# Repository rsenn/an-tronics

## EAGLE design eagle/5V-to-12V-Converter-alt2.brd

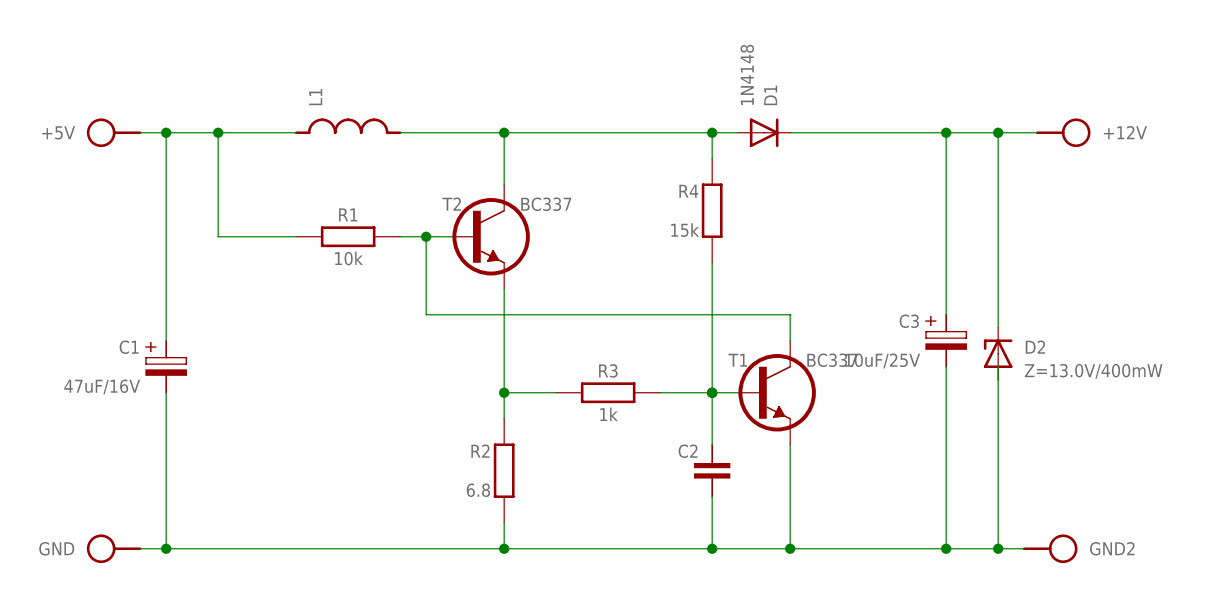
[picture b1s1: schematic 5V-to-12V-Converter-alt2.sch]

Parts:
+5V, +12V: SPAD
C1: 47uF/16V; E2.5-4/V
C2: C050-025X075
C3: 10uF/25V; E2.5-4/V
D1: 1N4148; DO34-7
D2: Z=13.0V/400mW; DO34Z10V
GND, GND2: SPAD
L1: L-SHORT02/5; L-02/5V
R1: 10k; 0204/10
R2: 6.8; 0204/10
R3: 1k; 0204/10
R4: 15k; 0204/10
T1, T2: BC337; TO92-CBE

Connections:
unnamed: R1.2, T1.C, T2.B
unnamed: +5V.1, C1.+, L1.2, R1.1
unnamed: +12V.1, C3.+, D1.C, D2.C
unnamed: C1.-, C2.2, C3.-, D2.A, GND.1, GND2.1, R2.1 (2), T1.E
unnamed: R2.2 (1), R3.1, T2.E
unnamed: C2.1, R3.2, R4.1 (2), T1.B
unnamed: D1.A, L1.1, R4.2 (1), T2.C

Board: 2 copper layers, 16 parts (0 on the bottom side), 7 nets, no tracks yet.

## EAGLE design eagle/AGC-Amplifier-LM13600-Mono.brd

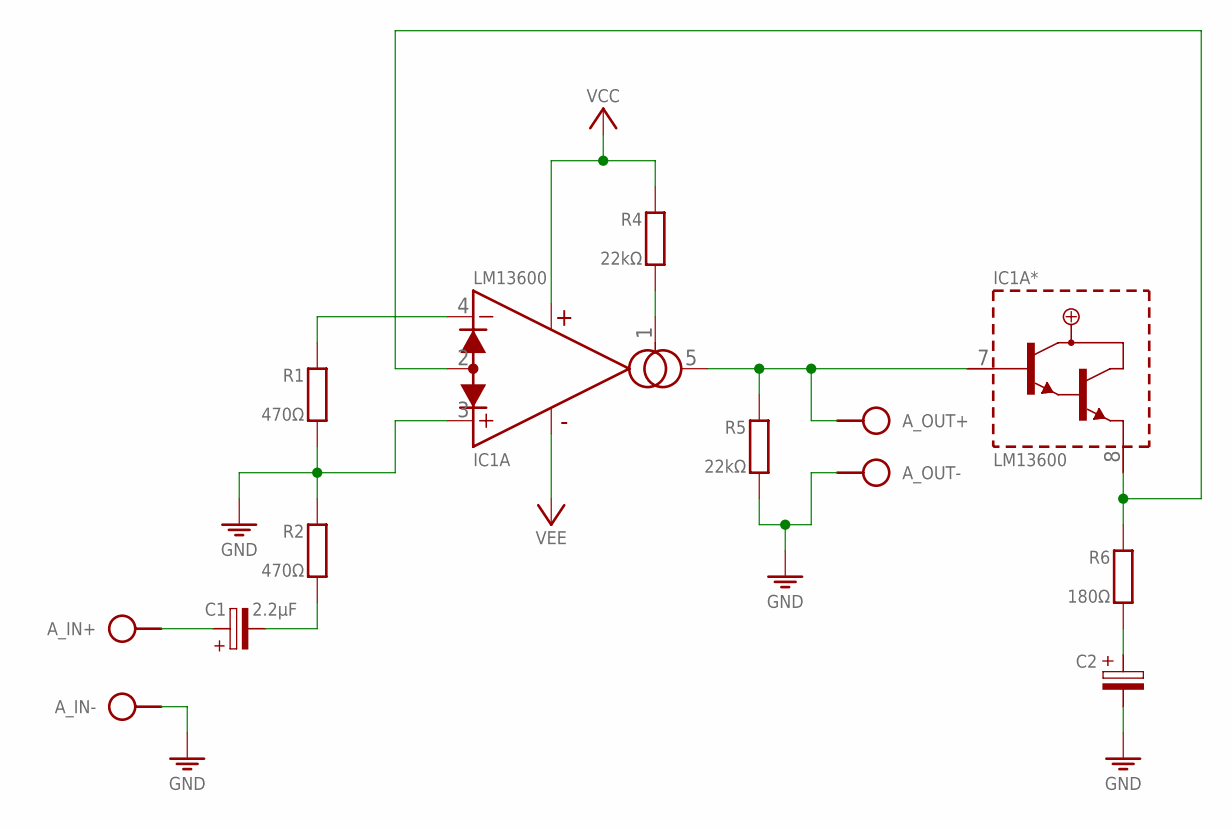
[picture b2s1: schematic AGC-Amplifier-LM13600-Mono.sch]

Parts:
A_IN: SPAD+-+-; SPAD+-
A_OUT: SPAD+-+-; SPAD+-
C1: 2.2μF; E2.5-4/V
C2: CPOLE2,5-4/V; E2.5-4/V
IC1: LM13600; DIL16
PWR: VCC_GND_VEEPWR-+GND-; SPAD-PWR-+GND-
R1: 470Ω; 0202/7
R2: 470Ω; 0202/7-V
R4: 22kΩ; 0202/7
R5: 22kΩ; 0202/7-V
R6: 180Ω; 0202/7

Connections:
GND: A_IN.1, A_OUT.1, C2.-, IC1.3 (+IN), PWR.GND, R1.2, R2.1, R5.2
unnamed: IC1.1 (AMP/BIAS), R4.2
unnamed: C1.-, R2.2
unnamed: C2.+, R6.2
unnamed: IC1.4 (-IN), R1.1
unnamed: IC1.2 (DIODE/BIAS), IC1.8 (BUFF/OUT), R6.1
unnamed: A_IN.2, C1.+
unnamed: A_OUT.2, IC1.5 (OUT), IC1.7 (BUFF/IN), R5.1
VCC: IC1.11 (V+), PWR.VCC, R4.1
VEE: IC1.6 (V-), PWR.VEE

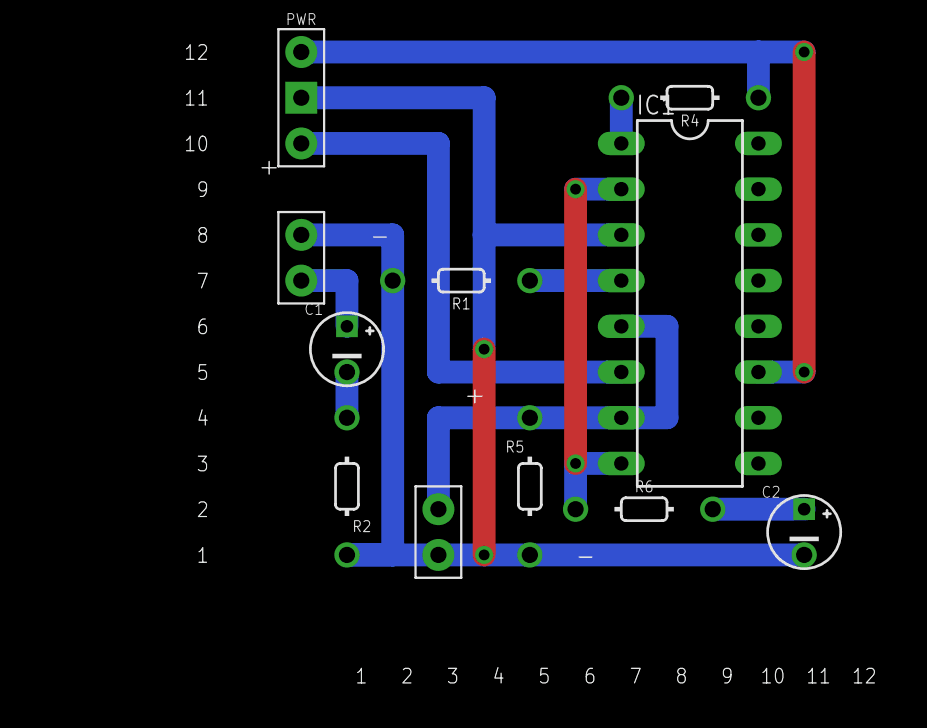
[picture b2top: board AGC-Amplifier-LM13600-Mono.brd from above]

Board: 2 copper layers, 11 parts (0 on the bottom side), 10 nets.

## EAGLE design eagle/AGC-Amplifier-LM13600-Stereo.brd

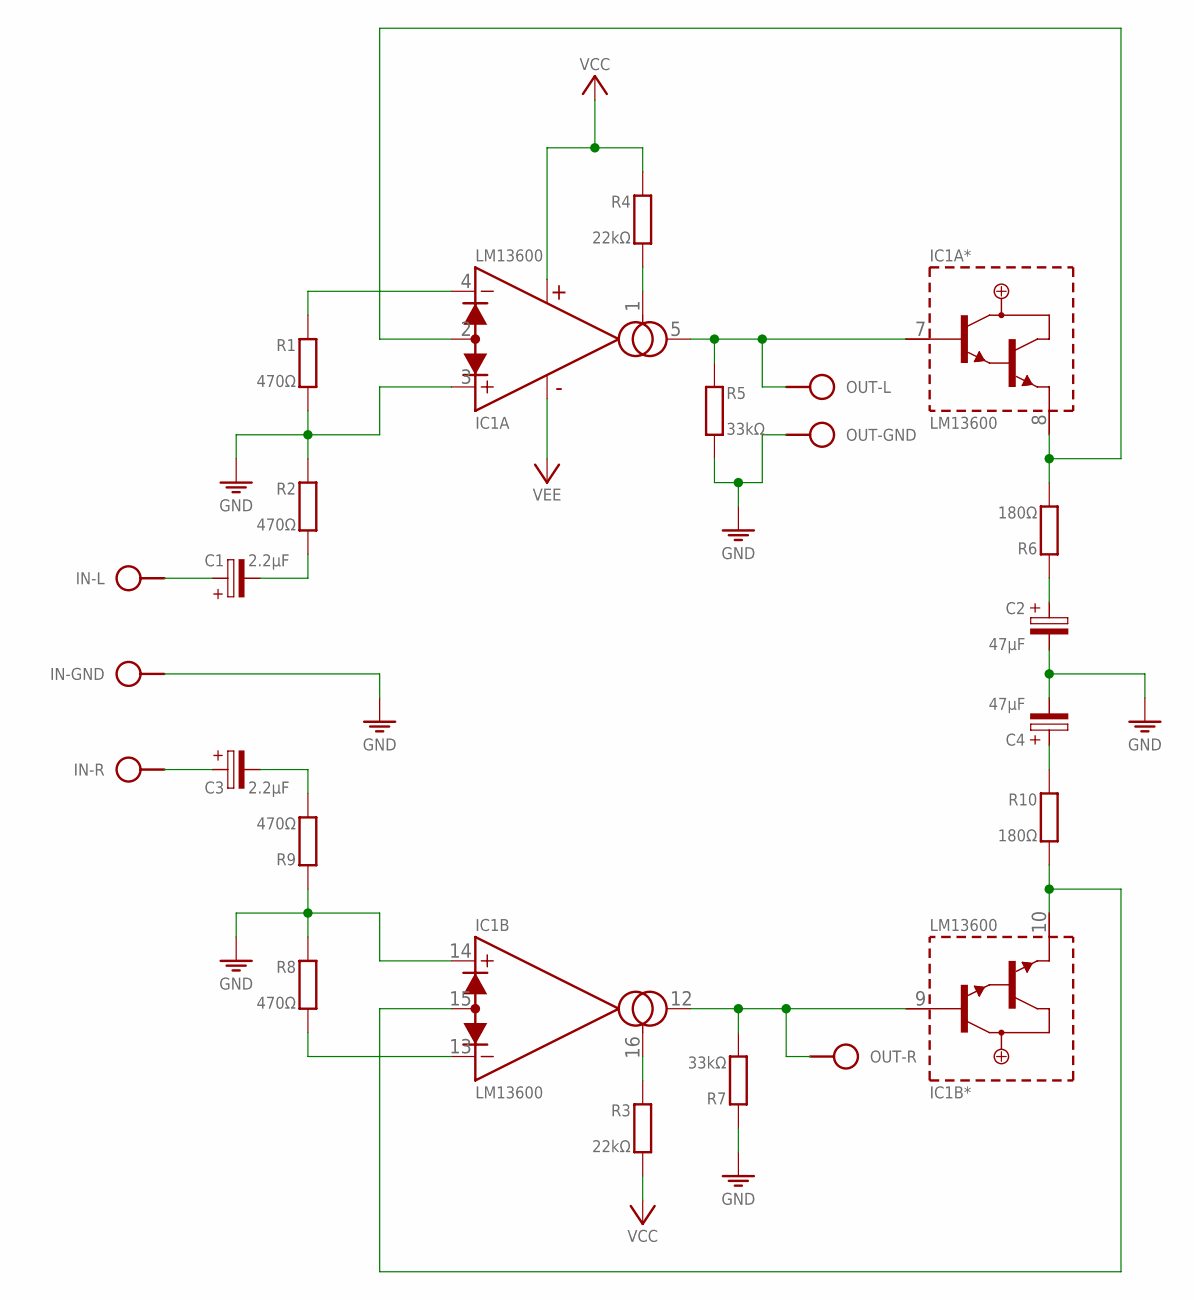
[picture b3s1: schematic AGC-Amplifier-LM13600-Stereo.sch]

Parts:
C1, C3: 2.2μF; E2,5-4
C2, C4: 47μF; E2.5-4/V
IC1: LM13600; DIL16
IN: SAUDIOL-GND-R; SPAD-L-GND-R
OUT: SAUDIO; SPAD-3
PWR: VCC_GND_VEEPWR--GND+; SPAD-PWR--GND+
R1, R8, R9: 470Ω; 0202/7-V
R2: 470Ω; 0202/7
R3, R4: 22kΩ; 0202/7
R5, R7: 33kΩ; 0202/7-V
R6, R10: 180Ω; 0202/7-V

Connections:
GND: C2.-, C4.-, IC1.3 (+IN), IC1.14 (+IN), IN.0, OUT.2, PWR.GND, R1.2, R2.1, R5.2, R7.1, R8.1, R9.1
unnamed: IC1.1 (AMP/BIAS), R4.2
unnamed: C1.-, R2.2
unnamed: C2.+, R6.1
unnamed: IC1.4 (-IN), R1.1
unnamed: IC1.2 (DIODE/BIAS), IC1.8 (BUFF/OUT), R6.2
unnamed: C1.+, IN.L
unnamed: IC1.5 (OUT), IC1.7 (BUFF/IN), OUT.1, R5.1
unnamed: IC1.16 (AMP/BIAS), R3.1
unnamed: C3.-, R9.2
unnamed: IC1.13 (-IN), R8.2
unnamed: IC1.10 (BUFF/OUT), IC1.15 (DIODE/BIAS), R10.2
unnamed: C4.+, R10.1
unnamed: IC1.9 (BUFF/IN), IC1.12 (OUT), OUT.3, R7.2
unnamed: C3.+, IN.R
VCC: IC1.11 (V+), PWR.VCC, R3.2, R4.1
VEE: IC1.6 (V-), PWR.VEE

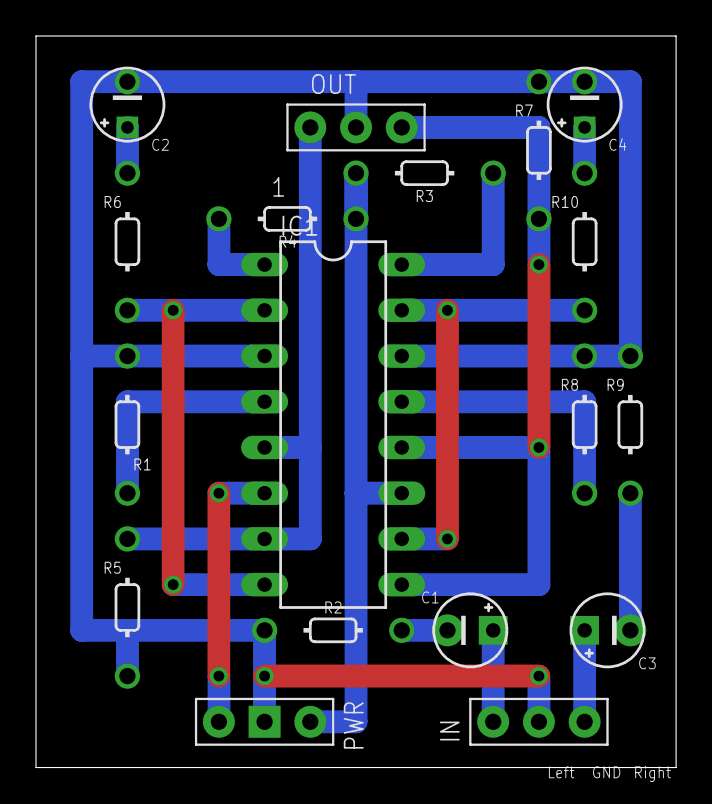
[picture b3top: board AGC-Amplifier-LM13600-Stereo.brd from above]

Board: 2 copper layers, 35.6 x 40.6 mm, 18 parts (0 on the bottom side), 17 nets.

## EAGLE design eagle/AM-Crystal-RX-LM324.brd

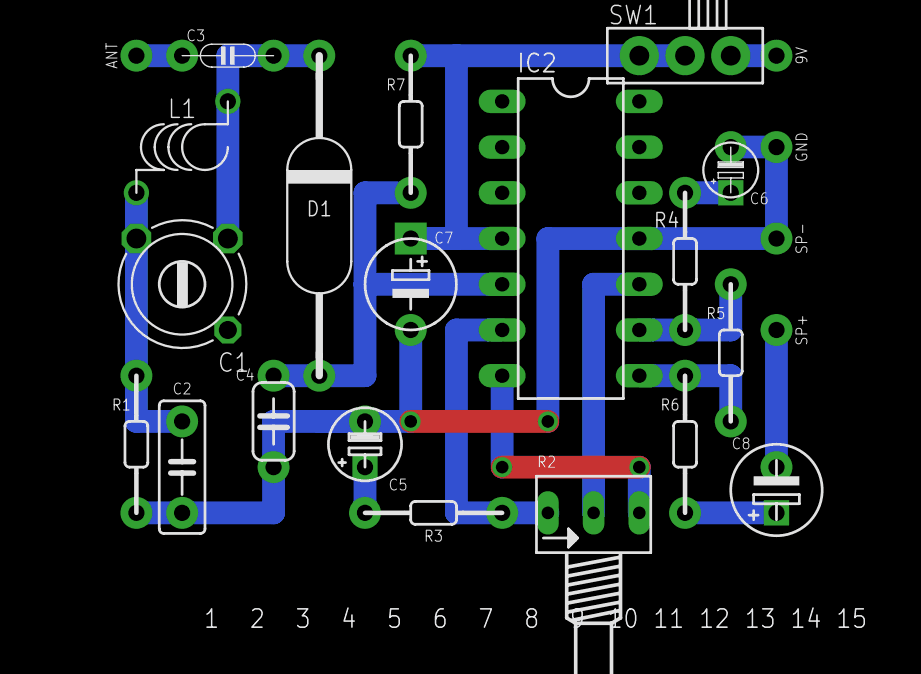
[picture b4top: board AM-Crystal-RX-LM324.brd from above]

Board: 2 copper layers, 24 parts (0 on the bottom side), 16 nets.

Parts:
9V: BAT+; SPAD
ANT: ANT; SPAD
C1: 5-18pF; TRIM808-45
C2: 10nF; C050-025X075/V
C3: 1.5pF; C050-020X036
C4: 330pF; C050-024X044/V
C5: 1μF; E2.5-4/V
C6: 1μF; E2,5-3/V
C7: 100μF; E5-5/V
C8: 100μF; E2,5-5/V
D1: OA79; OA79-18/V
GND: BAT-; SPAD
IC2: LM324; DIL14
L1: 0.15μH; L-04-5/5
R1, R7: 1MΩ; 0202/7-V
R2: 100kΩ; B64Y
R3: 3.3kΩ; 0202/7
R4: 3.3kΩ; 0202/7-V
R5: 100kΩ; 0202/7-V
R6: 100Ω; 0202/7-V
SP+: SPKR+; SPAD
SP-: SPKR-; SPAD
SW1: SL-SW-1P-2T-H; SLSW-1P2T-H

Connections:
A: IC2.7, R2.A
E: IC2.6, R2.E, R3.1
GND: C2.2, C4.2, C5.-, C6.-, C7.-, GND.1, IC2.11, R1.2, SP-.1
unnamed: C4.1, D1.A, IC2.5, R7.2
unnamed: C7.+, IC2.4, R7.1, SW1.P
unnamed: C1.1, C2.1, L1.1, R1.1
unnamed: C1.2, C3.2, D1.C, L1.2
unnamed: ANT.1, C3.1
unnamed: IC2.8, R5.2, R6.1
unnamed: IC2.9, R4.1, R5.1
unnamed: C5.+, R3.2
unnamed: C6.+, R4.2
unnamed: C8.+, R6.2
unnamed: C8.-, SP+.1
unnamed: 9V.1, SW1.O
S: IC2.10, R2.S

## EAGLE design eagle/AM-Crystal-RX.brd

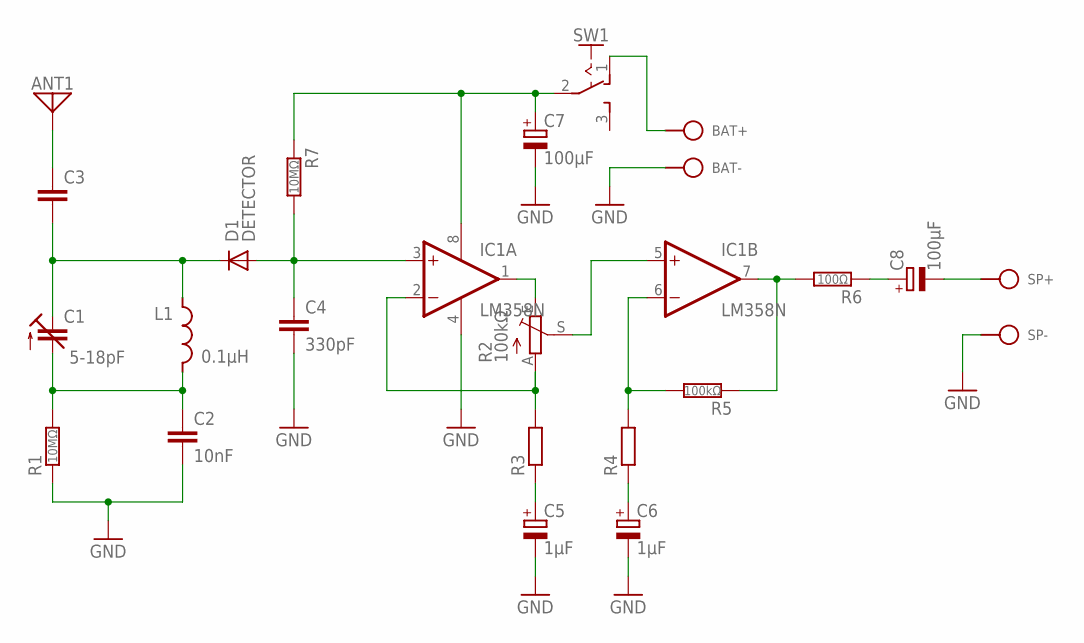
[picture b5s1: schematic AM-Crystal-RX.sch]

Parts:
ANT1: ANT; SPAD
BAT+: BAT+; SPAD
BAT-: BAT-; SPAD
C1: 5-18pF; TRIM-2222-808
C2: 10nF; C050-025X075
C3: C025-015X024
C4: 330pF; C050-024X044
C5, C6: 1μF; E2,5-3
C7, C8: 100μF; E2,5-5
D1: DETECTOR; DO34-10
IC1: LM358N; DIL08
L1: 0.1μH; L-04/10
R1: 10MΩ; 0202/7-V
R2: 100kΩ; B64Y
R3, R4: R0202/7; 0202/7
R5: 100kΩ; 0202/7
R6: 100Ω; 0202/7
R7: 10MΩ; 0202/7
SP+: SPKR+; SPAD
SP-: SPKR-; SPAD
SW1: SL-SW-1P-2T-H; SLSW-1P2T-H

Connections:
GND: BAT-.1, C2.2, C4.2, C5.-, C6.-, C7.-, IC1.4 (V-), R1.1, SP-.1
unnamed: C4.1, D1.A, IC1.3 (+IN), R7.2
unnamed: C7.+, IC1.8 (V+), R7.1, SW1.2
unnamed: C1.2 (E), C2.1, L1.2, R1.2
unnamed: IC1.2 (-IN), R2.A, R3.2
unnamed: C1.1 (A), C3.2, D1.C, L1.1
unnamed: ANT1.1, C3.1
unnamed: IC1.1 (OUT), R2.E
unnamed: IC1.5 (+IN), R2.S
unnamed: IC1.7 (OUT), R5.1, R6.2
unnamed: IC1.6 (-IN), R4.2, R5.2
unnamed: C5.+, R3.1
unnamed: C6.+, R4.1
unnamed: C8.+, R6.1
unnamed: C8.-, SP+.1
unnamed: BAT+.1, SW1.1 (O)

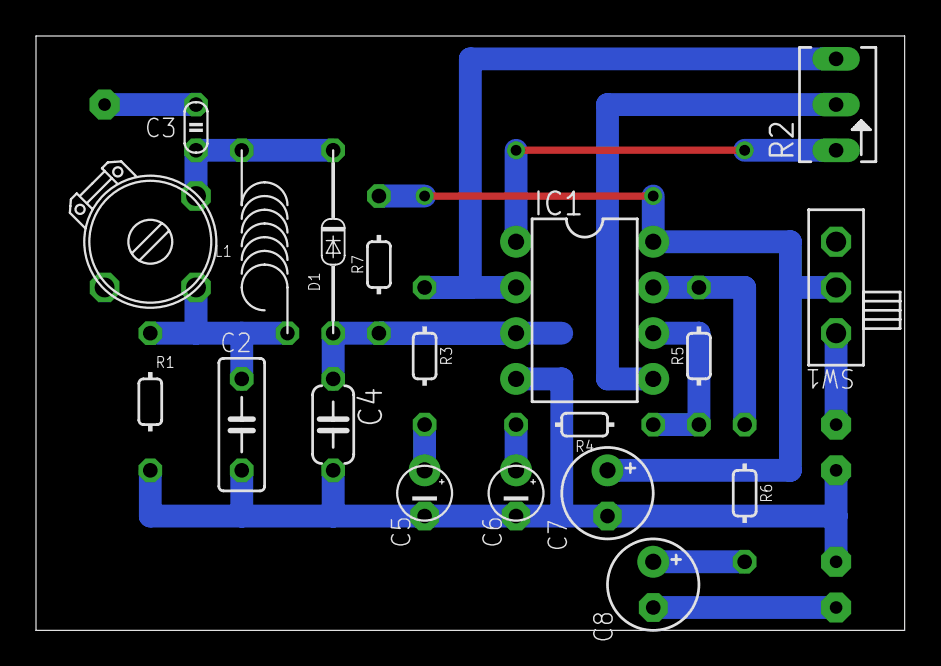
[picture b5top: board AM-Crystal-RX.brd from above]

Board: 2 copper layers, 48.3 x 33.0 mm, 24 parts (0 on the bottom side), 16 nets.

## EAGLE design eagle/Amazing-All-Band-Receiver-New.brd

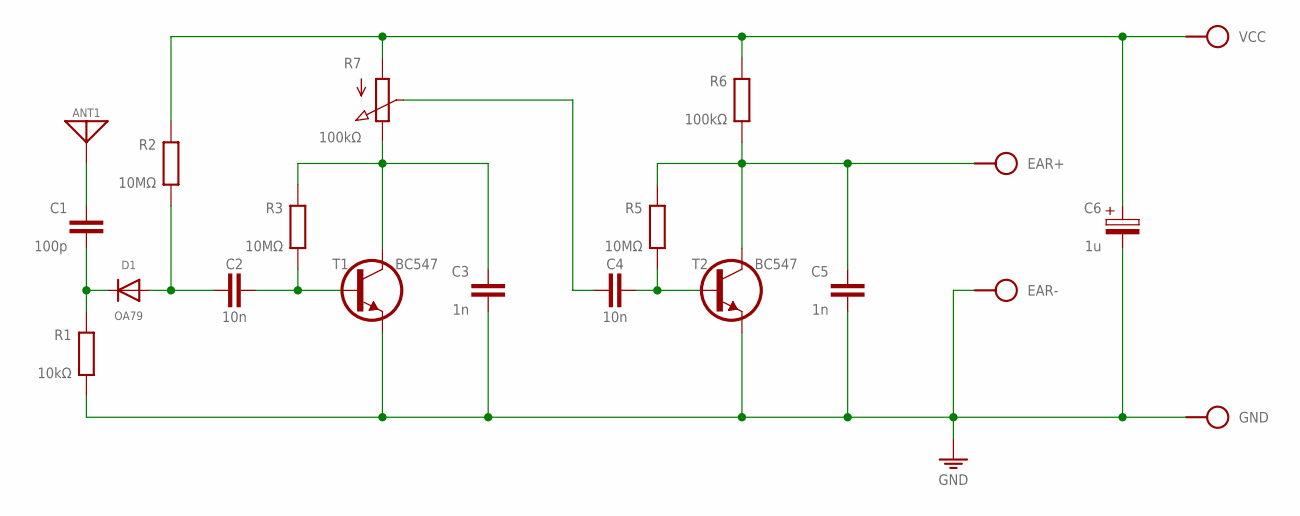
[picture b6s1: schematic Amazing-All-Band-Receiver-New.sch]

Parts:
ANT1: ANT; SPAD
C1: 100p; C050-020X036/V
C2, C4: 10n; C050-020X036
C3, C5: 1n; C050-020X036
C6: 1u; E2,5-3
D1: OA79; DO34-7V
EAR+: SPAD
EAR-: SPAD
GND: SPAD
R1: 10kΩ; 0202/7-V
R2: 10MΩ; 0202/7
R3, R5: 10MΩ; 0202/7-V
R6: 100kΩ; 0202/7-V
R7: 100kΩ; POT
T1, T2: BC547; TO92-CBE
VCC: SPAD

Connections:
AC: C1.2, D1.C, R1.2
ANT: ANT1.1, C1.1
DC: C2.2, D1.A, R2.1
GND: C3.2, C5.2, C6.-, EAR-.1, GND.1, R1.1, T1.E, T2.E
I1: C2.1, R3.1, T1.B
I2: C4.1, R5.1, T2.B
O1: C3.1, R3.2, R7.3 (E), T1.C
O2: C5.1, EAR+.1, R5.2, R6.1, T2.C
VCC: C6.+, R2.2, R6.2, R7.1 (A), VCC.1
VO1: C4.2, R7.2 (S)

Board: 2 copper layers, 20 parts (0 on the bottom side), 10 nets, no tracks yet.
